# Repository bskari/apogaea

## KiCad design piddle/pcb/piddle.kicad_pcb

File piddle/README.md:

Piddle
======

Sound reactive LED strips, originating from a central point and placed in a
geodesic dome. Running on a custom PCB with ESP32.

Wiring
------

- LED pins: see source
- Microphone
  - SCK: 19
  - WS: 22
  - SD: 21
  - L/R: ground
  - VDD: 3.3V
  - GND: ground

Hardware
--------

- ESP32 WROOM 32
- I2S microphone
- 15 WS2812B LED strips

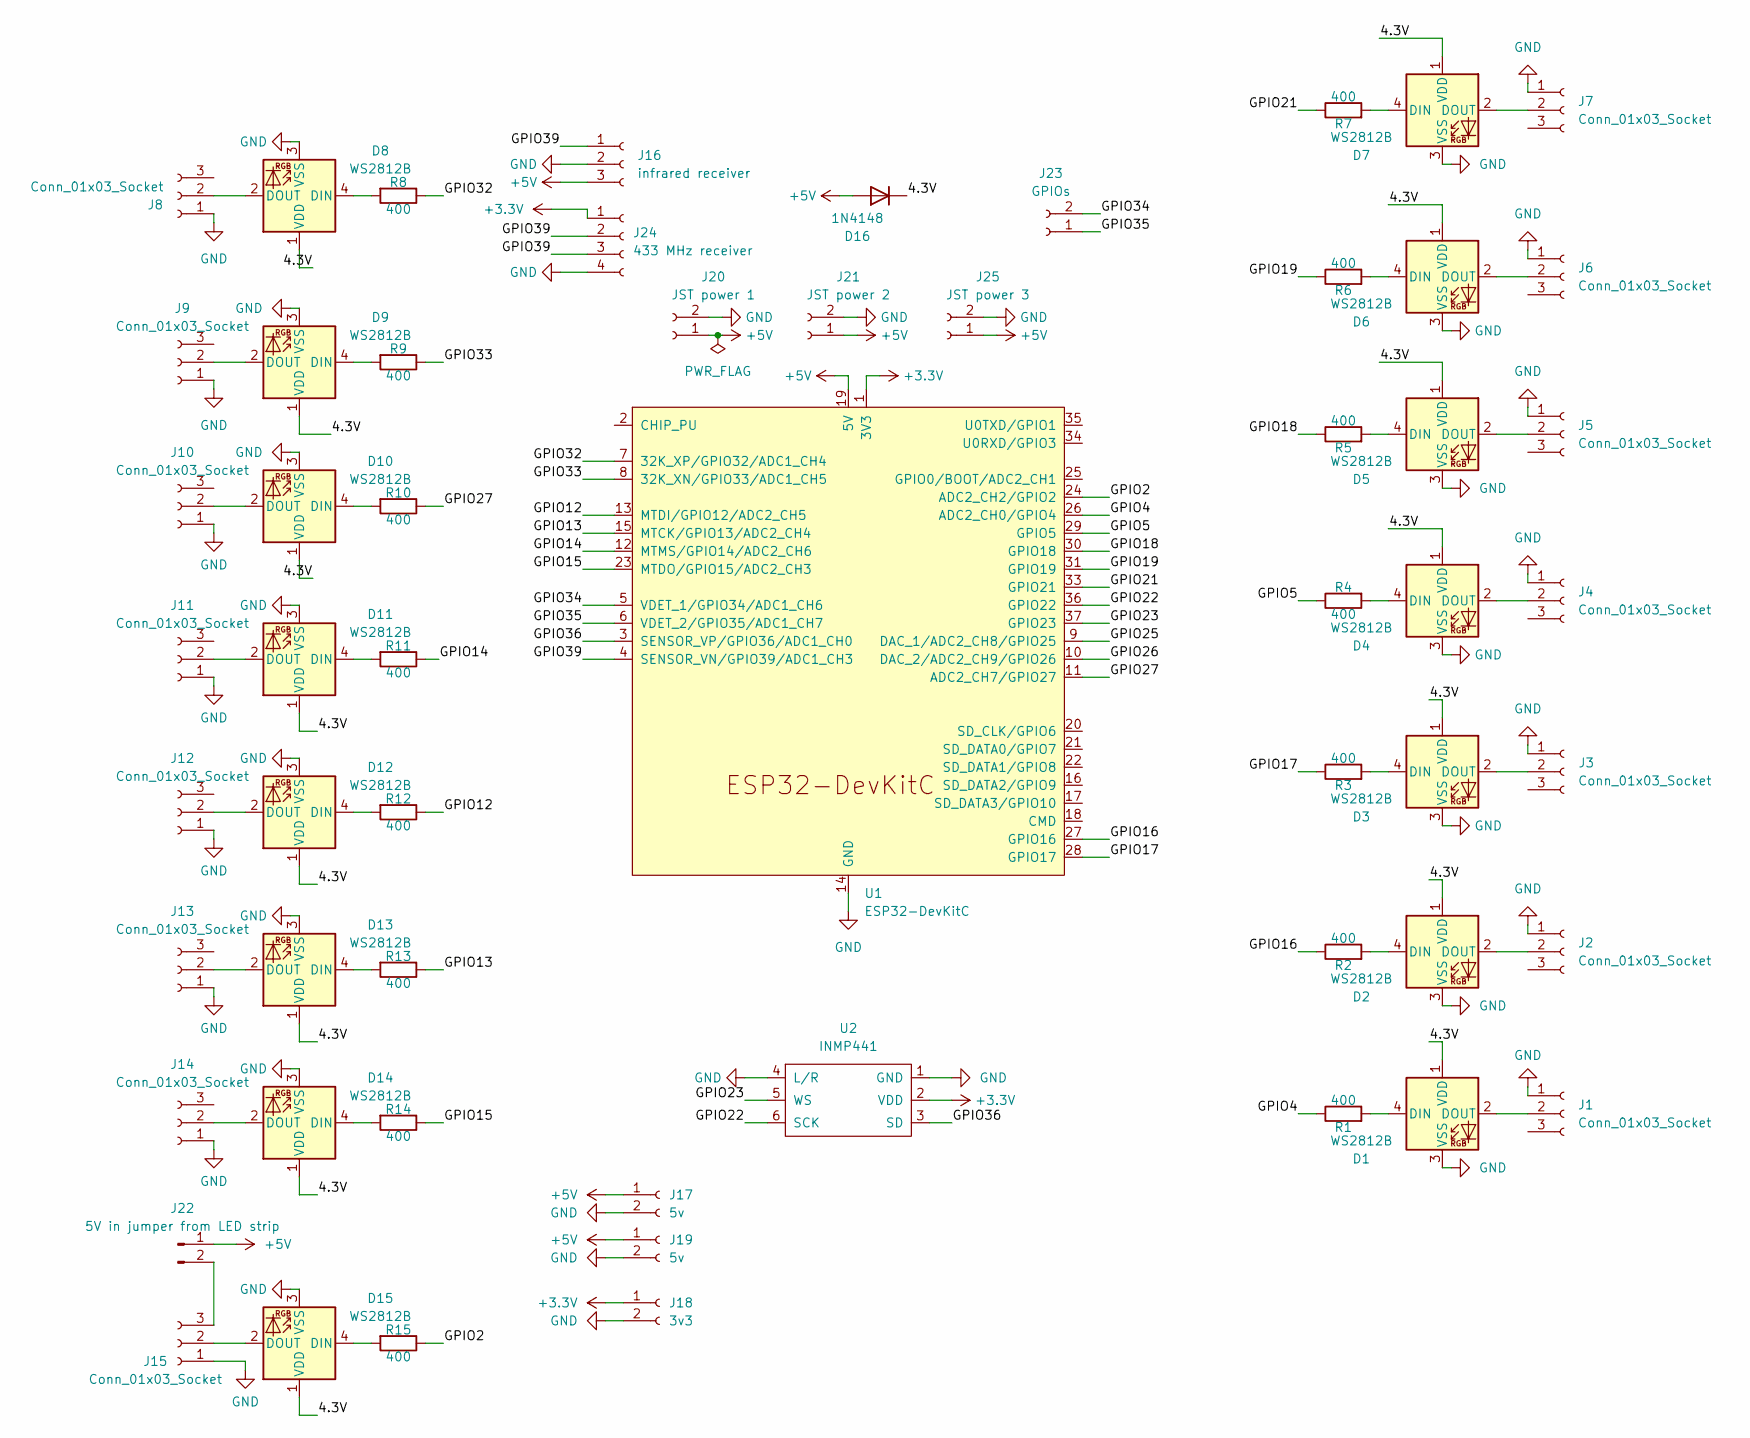
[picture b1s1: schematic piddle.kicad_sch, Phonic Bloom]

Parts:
D1, D2, D3, D4, D5, D6, D7, D8, D9, D10, D11, D12, D13, D14, D15: WS2812B; LED_WS2812B_PLCC4_5.0x5.0mm_P3.2mm
D16: 1N4148; D_DO-35_SOD27_P10.16mm_Horizontal
J1, J2, J3, J4, J5, J6, J7, J8, J9, J10, J11, J12, J13, J14, J15: Conn_01x03_Socket; PinHeader_1x03_P2.54mm_Vertical
J16: infrared receiver; PinHeader_1x03_P2.54mm_Vertical
J17, J19: 5v; PinHeader_1x02_P2.54mm_Vertical
J18: 3v3; PinHeader_1x02_P2.54mm_Vertical
J20: JST power 1; JST_PH_S2B-PH-K_1x02_P2.00mm_Horizontal
J21: JST power 2; JST_PH_S2B-PH-K_1x02_P2.00mm_Horizontal
J22: 5V in jumper from LED strip; PinHeader_1x02_P2.54mm_Vertical
J23: GPIOs; PinHeader_1x02_P2.54mm_Vertical
J24: 433 MHz receiver; PinHeader_1x04_P2.54mm_Vertical
J25: JST power 3; JST_PH_S2B-PH-K_1x02_P2.00mm_Horizontal
R1, R2, R3, R4, R5, R6, R7, R8, R9, R10, R11, R12, R13, R14, R15: 400; R_1206
U1: ESP32-DevKitC
U2: INMP441; inmp441

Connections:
+3.3V: J18.1, J24.1, U1.1 (3V3), U2.2 (VDD); also elsewhere on the board
+5V: D16.2 (A), J16.3, J17.1, J19.1, J20.1, J21.1, J22.1, J25.1, U1.19 (5V)
/4.3V: D1.1 (VDD), D2.1 (VDD), D3.1 (VDD), D4.1 (VDD), D5.1 (VDD), D6.1 (VDD), D7.1 (VDD), D8.1 (VDD), D9.1 (VDD), D10.1 (VDD), D11.1 (VDD), D12.1 (VDD), D13.1 (VDD), D14.1 (VDD), D15.1 (VDD), D16.1 (K)
/GPIO2: R15.1, U1.24 (ADC2_CH2/GPIO2)
/GPIO4: R1.1, U1.26 (ADC2_CH0/GPIO4)
/GPIO5: R4.1, U1.29 (GPIO5)
/GPIO12: R12.1, U1.13 (MTDI/GPIO12/ADC2_CH5)
/GPIO13: R13.1, U1.15 (MTCK/GPIO13/ADC2_CH4)
/GPIO14: R11.1, U1.12 (MTMS/GPIO14/ADC2_CH6)
/GPIO15: R14.1, U1.23 (MTDO/GPIO15/ADC2_CH3)
/GPIO16: R2.1, U1.27 (GPIO16)
/GPIO17: R3.1, U1.28 (GPIO17)
/GPIO18: R5.1, U1.30 (GPIO18)
/GPIO19: R6.1, U1.31 (GPIO19)
/GPIO21: R7.1, U1.33 (GPIO21)
/GPIO22: U1.36 (GPIO22), U2.6 (SCK)
/GPIO23: U1.37 (GPIO23), U2.5 (WS)
/GPIO25: U1.9 (DAC_1/ADC2_CH8/GPIO25)
/GPIO26: U1.10 (DAC_2/ADC2_CH9/GPIO26)
/GPIO27: R10.1, U1.11 (ADC2_CH7/GPIO27)
/GPIO32: R8.1, U1.7 (32K_XP/GPIO32/ADC1_CH4)
/GPIO33: R9.1, U1.8 (32K_XN/GPIO33/ADC1_CH5)
/GPIO34: J23.2, U1.5 (VDET_1/GPIO34/ADC1_CH6)
/GPIO35: J23.1, U1.6 (VDET_2/GPIO35/ADC1_CH7)
/GPIO36: U1.3 (SENSOR_VP/GPIO36/ADC1_CH0), U2.3 (SD)
/GPIO39: J16.1, J24.2, J24.3, U1.4 (SENSOR_VN/GPIO39/ADC1_CH3); also elsewhere on the board
GND: D1.3 (VSS), D2.3 (VSS), D3.3 (VSS), D4.3 (VSS), D5.3 (VSS), D6.3 (VSS), D7.3 (VSS), D8.3 (VSS), D9.3 (VSS), D10.3 (VSS), D11.3 (VSS), D12.3 (VSS), D13.3 (VSS), D14.3 (VSS), D15.3 (VSS), J1.1, J2.1, J3.1, J4.1, J5.1, J6.1, J7.1, J8.1, J9.1, J10.1, J11.1, J12.1, J13.1, J14.1, J15.1, J16.2, J17.2, J18.2, J19.2, J20.2, J21.2, J24.4, J25.2, U1.14 (GND), U1.32 (GND), U1.38 (GND), U2.1 (GND), U2.4 (L/R); also elsewhere on the board
unnamed: D1.4 (DIN), R1.2
unnamed: D1.2 (DOUT), J1.2
unnamed: D2.4 (DIN), R2.2
unnamed: D2.2 (DOUT), J2.2
unnamed: D3.4 (DIN), R3.2
unnamed: D3.2 (DOUT), J3.2
unnamed: D4.4 (DIN), R4.2
unnamed: D4.2 (DOUT), J4.2
unnamed: D5.4 (DIN), R5.2
unnamed: D5.2 (DOUT), J5.2
unnamed: D6.4 (DIN), R6.2
unnamed: D6.2 (DOUT), J6.2
unnamed: D7.4 (DIN), R7.2
unnamed: D7.2 (DOUT), J7.2
unnamed: D8.4 (DIN), R8.2
unnamed: D8.2 (DOUT), J8.2
unnamed: D9.4 (DIN), R9.2
unnamed: D9.2 (DOUT), J9.2
unnamed: D10.4 (DIN), R10.2
unnamed: D10.2 (DOUT), J10.2
unnamed: D11.4 (DIN), R11.2
unnamed: D11.2 (DOUT), J11.2
unnamed: D12.4 (DIN), R12.2
unnamed: D12.2 (DOUT), J12.2
unnamed: D13.4 (DIN), R13.2
unnamed: D13.2 (DOUT), J13.2
unnamed: D14.4 (DIN), R14.2
unnamed: D14.2 (DOUT), J14.2
unnamed: D15.4 (DIN), R15.2
unnamed: D15.2 (DOUT), J15.2
unnamed: J15.3, J22.2

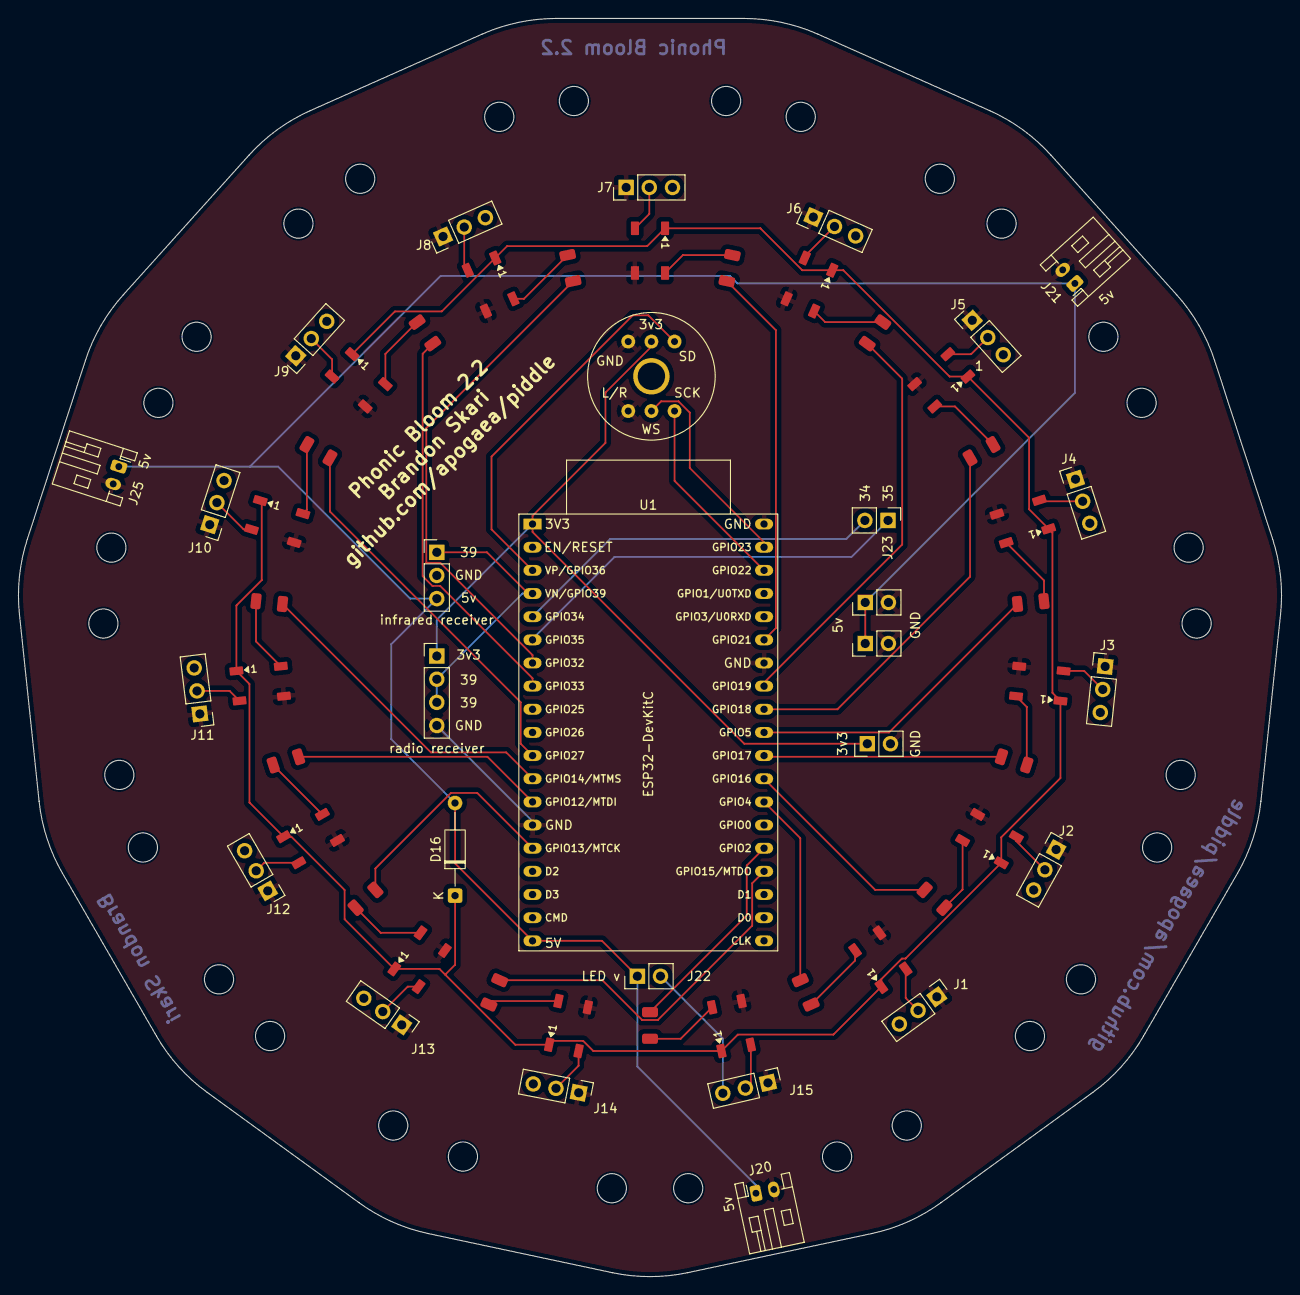
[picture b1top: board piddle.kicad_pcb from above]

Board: 2 copper layers, 138.6 x 138.0 mm, 58 parts (0 on the bottom side), 56 nets.

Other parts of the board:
radio receiver: 433 MHz receiver; PinHeader_1x04_P2.54mm_Vertical

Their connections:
+3.3V: radio receiver.1; also elsewhere on the board
/GPIO39: radio receiver.2, radio receiver.3; also elsewhere on the board
GND: radio receiver.4; also elsewhere on the board

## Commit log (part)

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2025-03-23 15 pins
2025-04-06 Get 10 outputs working
2025-04-06 Remove double ended
2025-04-11 Remove LEDs
2025-04-11 Limit to 6A using brightness
2025-04-13 Increase sensitivity
2025-04-13 Shut off the ends of the strips
2025-04-21 Add day parameter so that we can use the power sim for BM
2025-04-21 Fix day labels on matplot
2025-04-23 Add vertical lines for days
2025-04-26 Add day charge option
2025-04-26 Change day charge option to time
2025-04-26 Don't day charge past 6 PM
2025-04-28 Add day charge until option
2025-05-04 Update voltage monitor for LiFePo4
2025-05-13 Add option to limit charge from controller
2025-05-13 Remove debug print
2025-05-13 Better colors
2025-05-14 Reword some messages
2025-05-19 Formatting print
2025-05-21 Add RemoteXY controls
2025-05-26 Add band normalization
2025-05-26 Partial boost bands
2025-05-26 FIxes
2025-07-12 Better upload scripts
2025-07-30 Start 15 pin
2025-07-30 Add initial entrance logo
2025-07-31 Mask off bottom of lotus
2025-08-03 Different arch design
2025-08-13 Update logo
2025-10-05 Add label to simulation plots
2025-11-15 Convert scons to Makefile
2025-11-15 Add sharp green
2025-11-15 Smooth green lines
2025-11-15 Add plasma waves hue
2025-12-07 Add horizontal comets (untested)
2025-12-07 Add mounting holes
2025-12-08 Process holes and cuts
2025-12-08 Arrange resistors
2025-12-08 Put arrange components in a function
2025-12-08 Sort and align more components
2025-12-09 Arrange LEDs
2025-12-09 Arrange LED positions too
2025-12-09 Arrange components for 15-strip board
2025-12-09 Add more headers for extra GPIOs, power, remote control
2025-12-10 More resistors in a bit
2025-12-11 Connect all components
2025-12-14 Update to KiCad 9
2025-12-21 Fix off-by-one error
2026-01-05 Rotate LED solder pads and update to workwith KiCad 9
2026-01-05 Update version on silkscreen
2026-01-05 Simplify and don't rearrange zones
2026-01-05 Fillet the edges
2026-02-10 Add Zed project settings
2026-02-10 Fix pins for 15-pin strip board
2026-02-12 Fix RemoteXY ifdef
2026-02-12 Print message on boot for how to quit serial monitor
2026-02-12 Update microphone pins
2026-02-12 Turn on the first LED for testing
2026-02-17 Put defines on the compile CLI
2026-02-18 Limit first LED brightness
2026-03-07 Add simulator
2026-03-07 Process multiple audio files
2026-03-07 Skip non-audio files
2026-03-10 Fix normalization
2026-03-10 Add Bluetooth
2026-03-10 Remove RemoteXY
2026-03-12 Add ArtNet support
2026-03-13 Try to tear down Bluetooth before doing ArtNet
2026-03-13 Toggle Bluetooth or Artnet behind ifdef guards
2026-03-13 Update power sim for 15 strips
2026-03-13 Add sliders to power_sim
2026-03-14 Increase power sim render speed
    - Cache ticks
    - Group segments by color
2026-03-17 Tweak sensitivity
2026-03-17 Change sensitivity
2026-03-22 Add repeating patterns every N LEDs
2026-03-23 Add tile offset
2026-03-23 Fix angle formatting for pads
2026-03-23 Change defaults
2026-03-23 Fix pin 25 blanking after ArtNet connection
2026-03-24 Avoid using GPIO 25 and 26 - they're used by DAC (and thus WiFi)
2026-03-24 Move pins around for RF radio module
2026-03-25 Don't use pins used by WiFi
2026-04-11 Add switch for v2.2 or v2.1 pins
2026-04-11 Disable the converter LEDs
2026-05-08 Toggle for showing converter LEDs
2026-05-11 Fix output on one strip
2026-05-23 Add 433 MHz radio receiver pins
2026-05-24 Clean up footprints from DRC
2026-05-24 Add ArtNet button and radio config
2026-05-25 Shut off LEDs when switching to ArtNwt
    try to fix stuck on LED
2026-05-25 Add timestamps to logs
2026-05-26 Put timing debug logging behind a toggle
2026-05-27 Simple ArtNet sender test
2026-05-30 Trying to make Artnet more responsive
2026-06-05 Add RemoteXY radio control
2026-06-05 Create soft AP
2026-06-07 Send channel toggles in radio
2026-06-07 Fix swap channel test mode
2026-06-07 Hide converter LEDs on ArtNet
2026-06-08 Du audio until ArtNet packets are received
2026-06-09 Require specifying pin version
